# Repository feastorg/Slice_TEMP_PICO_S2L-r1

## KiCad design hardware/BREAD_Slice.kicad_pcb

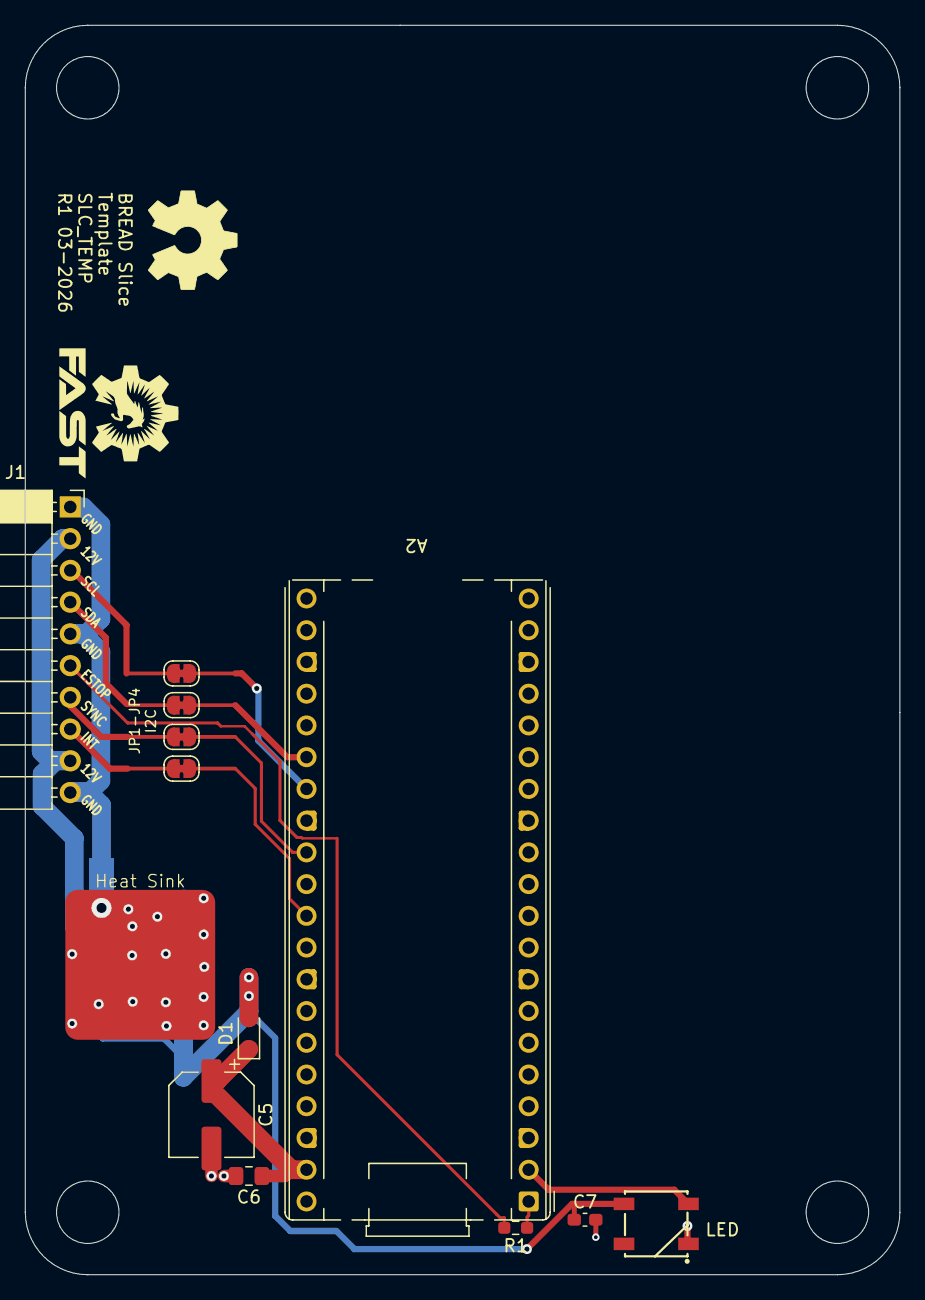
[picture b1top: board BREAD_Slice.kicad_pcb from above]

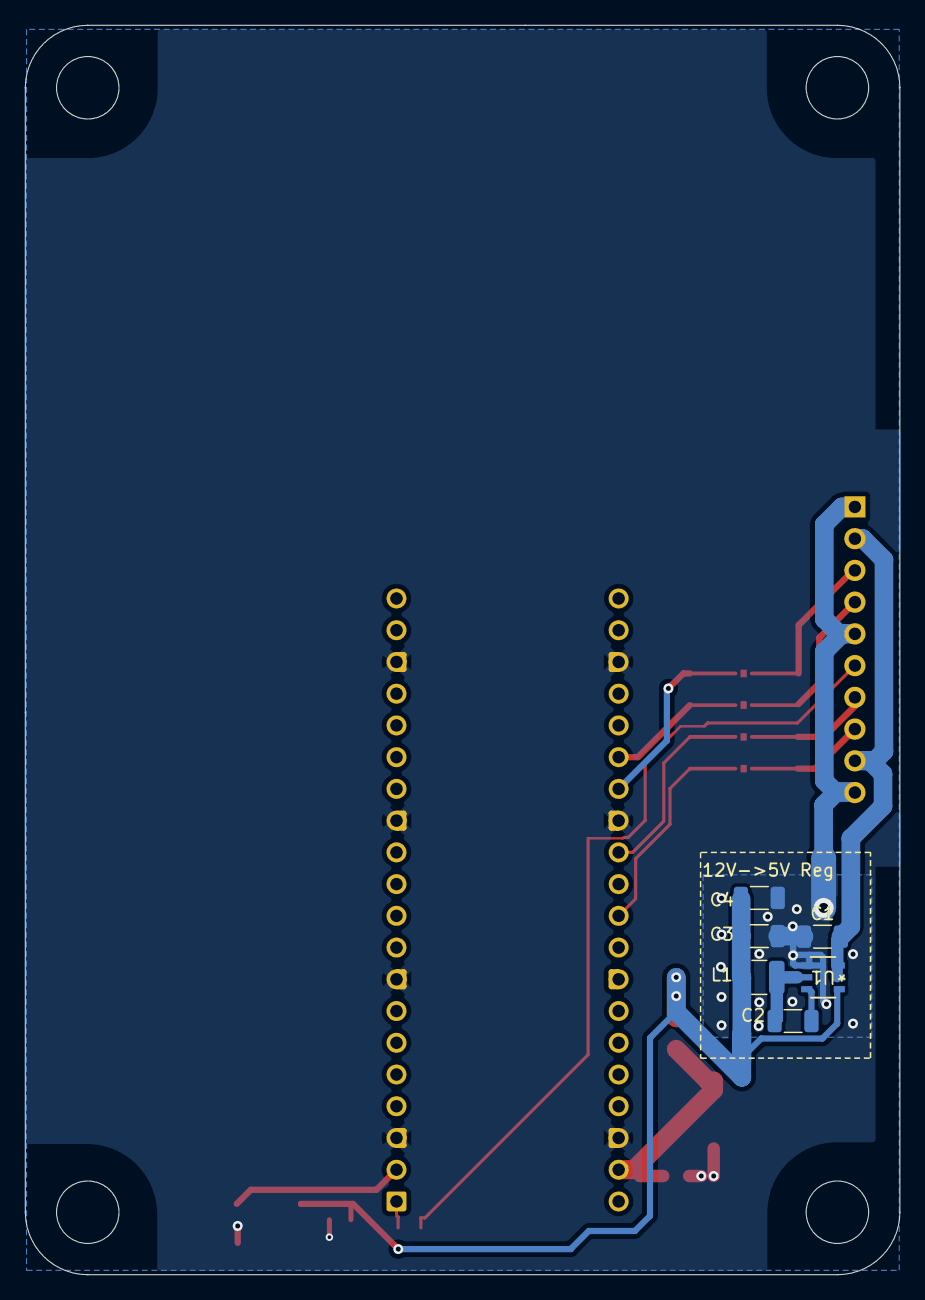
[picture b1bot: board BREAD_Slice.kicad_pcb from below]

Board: 2 copper layers, 70.0 x 100.0 mm, 25 parts (7 on the bottom side), 18 nets.

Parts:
A2: RaspberryPi_Pico; RaspberryPi_Pico_Common_THT
C1: 10u; C_1206_3216Metric
C2: 100nF; C_1206_3216Metric
C3, C4: 22uF; C_1206_3216Metric
C5: 47u 25V; CP_Elec_6.3x7.7
C6: 0.1u; C_0805_2012Metric_Pad1.18x1.45mm_HandSolder
C7: 100n; C_0603_1608Metric_Pad1.08x0.95mm_HandSolder
D1: BAT54WS-7-F; D_SOD-323_HandSoldering
D2: WS2812B_5050; WS2812-5050-4PIN
H1, H2, H3, H4: MountingHole; MountingHole_5mm
HS1: Heatsink_Pad; Thermal_Pad
J1: Conn_01x10_Socket; PinSocket_1x10_P2.54mm_Horizontal
JP1: I2C_CLK bus link; SolderJumper-2_P1.3mm_Bridged_RoundedPad1.0x1.5mm
JP2: I2C_DAT bus link; SolderJumper-2_P1.3mm_Bridged_RoundedPad1.0x1.5mm
JP3: SYNC bus link; SolderJumper-2_P1.3mm_Bridged_RoundedPad1.0x1.5mm
JP4: INT bus link; SolderJumper-2_P1.3mm_Bridged_RoundedPad1.0x1.5mm
L1: 4.7uH; L_1210_3225Metric
NT1: NetTie_2; NetTie-2_SMD_Pad2.0mm
R1: 1k; R_0603_1608Metric_Pad0.98x0.95mm_HandSolder
Ref**: Val**; OSHW_Logo_8mm
U1: AP63205; SOIC_05WU-7_DIO

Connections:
+5V: C3.2, C4.2, C7.1, D1.2 (A), D2.1 (VDD), L1.2, U1.1 (FB)
+12V: C1.2, J1.2, J1.9, U1.2 (EN), U1.3 (VIN)
/slice_template/ESTOP: J1.6, R1.1
/slice_template/ESTOP_MCU: A2.1 (GPIO0), R1.2
/slice_template/I2C0_CLK/GPIO21: A2.27 (GPIO21), JP1.2
/slice_template/I2C0_SDA/GPIO20: A2.26 (GPIO20), JP2.2
/slice_template/I2C_CLK: J1.3, JP1.1
/slice_template/I2C_DAT: J1.4, JP2.1
/slice_template/INT: J1.8, JP4.1
/slice_template/INT/CAN_{CS}: A2.31 (GPIO26_ADC0), JP4.2
/slice_template/LED: A2.2 (GPIO1), D2.4 (DIN)
/slice_template/SYNC: J1.7, JP3.1
/slice_template/SYNC/CAN_{INT}: A2.29 (GPIO22), JP3.2
/slice_template/VSYS: A2.39 (VSYS), C5.1, C6.1, D1.1 (K)
GND: A2.3 (GND), A2.8 (GND), A2.13 (GND), A2.18 (GND), A2.23 (GND), A2.28 (GND), A2.38 (GND), C1.1, C3.1, C4.1, C5.2, C6.2, C7.2, D2.3 (VSS), HS1.1, NT1.1, U1.4 (GND)
GNDPWR: J1.1, J1.5, J1.10, NT1.2
unnamed: C2.2, U1.6 (BST)
unnamed: C2.1, L1.1, U1.5 (SW)

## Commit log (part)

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2026-03-16 Changed to Pico from nano
2026-03-16 changed readme
2026-03-16 added i2c and spi
2026-03-16 add i2c level shifter in todo
2026-03-17 added level shifter and started layout
2026-03-17 finished layout
2026-03-17 added pins 2 and 3 to hierarchical sheet
2026-05-01 chore: untrack macos system files
2026-05-01 chore: untrack schematic backups
2026-05-01 pcb: minor changes and silk screen version
2026-05-01 chore: change version to v1 to align with template name
2026-05-01 fix: rewire gnd caps around pico
2026-05-01 📄 KiBot index + board renders (auto)
2026-05-20 Add slice.yaml manifest (schema v1.0)
2026-05-24 Add standardized TODO.md with Pass 1/Pass 2 structure
